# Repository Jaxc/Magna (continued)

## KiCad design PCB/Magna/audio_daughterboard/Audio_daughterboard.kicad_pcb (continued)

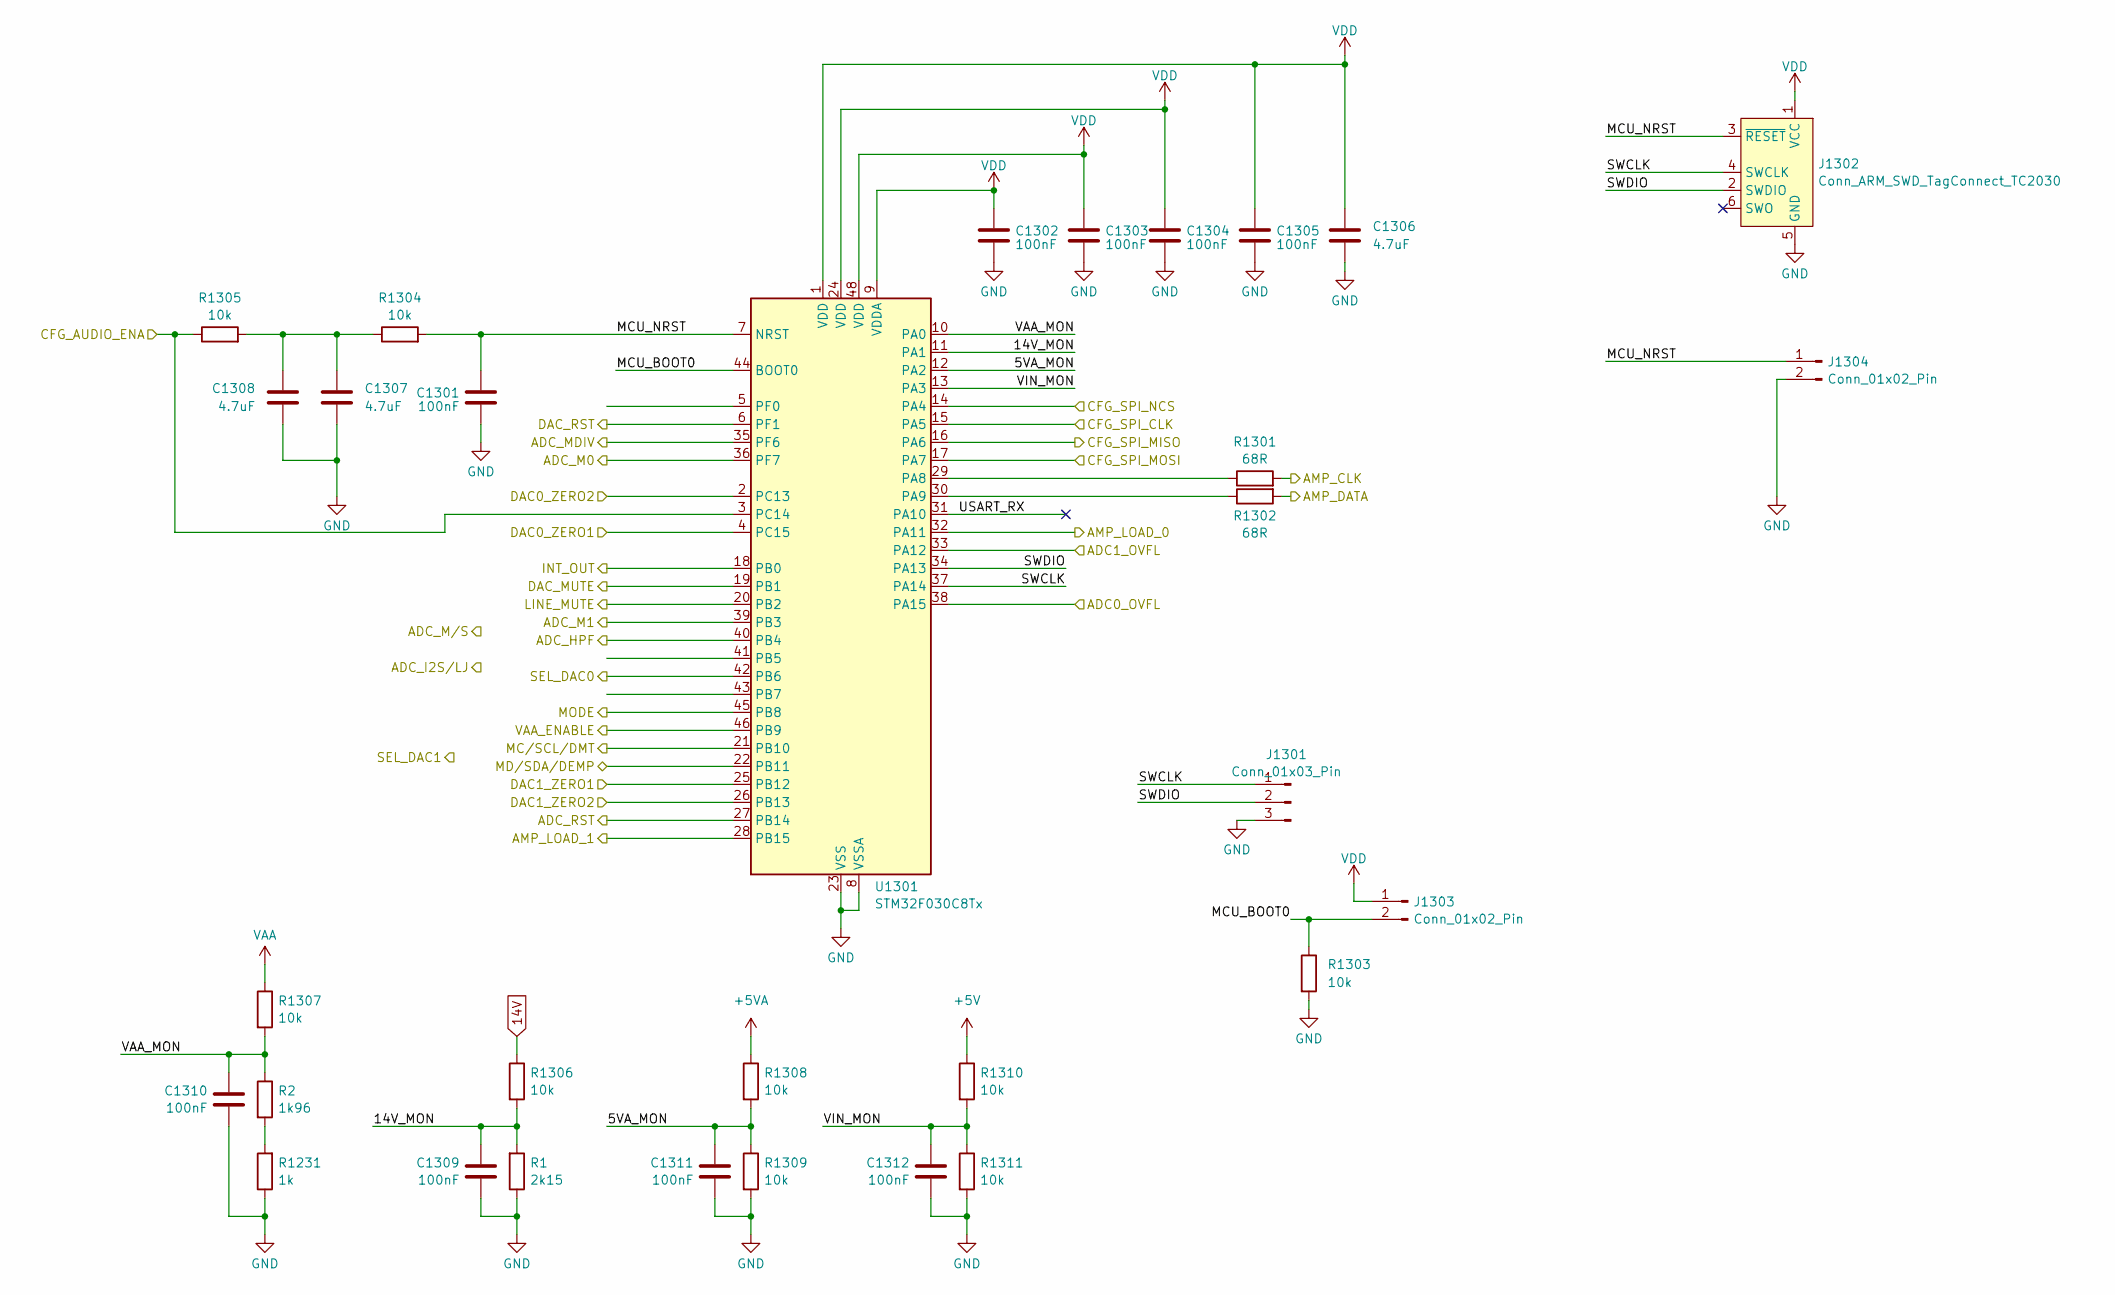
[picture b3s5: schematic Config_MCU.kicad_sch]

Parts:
C1301, C1302, C1303, C1304, C1305, C1309, C1310, C1311, C1312: 100nF; C_0603_1608Metric; LCSC C14663
C1306, C1307, C1308: 4.7uF; C_1206_3216Metric; LCSC C29823
J1301: Conn_01x03_Pin; PinHeader_1x03_P2.54mm_Vertical
J1302: Conn_ARM_SWD_TagConnect_TC2030; Tag-Connect_TC2030-IDC-FP_2x03_P1.27mm_Vertical
J1303, J1304: Conn_01x02_Pin; PinHeader_1x02_P2.54mm_Vertical
R1: 2k15; R_0603_1608Metric; LCSC C667562
R2: 1k96; R_0603_1608Metric; LCSC C160602
R1231: 1k; R_0603_1608Metric; LCSC C110776
R1301, R1302: 68R; R_0603_1608Metric; LCSC C351632
R1303, R1304, R1305, R1306, R1307, R1308, R1309, R1310, R1311: 10k; R_0603_1608Metric; LCSC C95204
U1301: STM32F030C8Tx; LQFP-48_7x7mm_P0.5mm; LCSC C23922

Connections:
14V: R1306.1; also elsewhere on the board
+5V: R1310.1; also elsewhere on the board
+5VA: R1308.1; also elsewhere on the board
/AUDIO_CFG_INT: U1301.18 (PB0); also elsewhere on the board
/AudioAdc0/ADC_HPF: U1301.40 (PB4); also elsewhere on the board
/AudioAdc0/ADC_M0: U1301.36 (PF7); also elsewhere on the board
/AudioAdc0/ADC_M1: U1301.39 (PB3); also elsewhere on the board
/AudioAdc0/ADC_MDIV: U1301.35 (PF6); also elsewhere on the board
/AudioAdc0/ADC_OVFL: U1301.38 (PA15); also elsewhere on the board
/AudioAdc0/ADC_RST: U1301.27 (PB14); also elsewhere on the board
/AudioAdc0/AMP_CLK: R1301.2; also elsewhere on the board
/AudioAdc0/AMP_DATA: R1302.2; also elsewhere on the board
/AudioAdc0/AMP_LOAD: U1301.32 (PA11); also elsewhere on the board
/AudioAdc1/ADC_OVFL: U1301.33 (PA12); also elsewhere on the board
/AudioAdc1/AMP_LOAD: U1301.28 (PB15); also elsewhere on the board
/AudioDac0/MC/SCL/DMT: U1301.21 (PB10); also elsewhere on the board
/AudioDac0/MD/SDA/DEMP: U1301.22 (PB11); also elsewhere on the board
/AudioDac0/MUTE: U1301.19 (PB1); also elsewhere on the board
/AudioDac0/ZERO1: U1301.25 (PB12); also elsewhere on the board
/AudioDac0/ZERO2: U1301.26 (PB13); also elsewhere on the board
/AudioDac0/~RST: U1301.6 (PF1); also elsewhere on the board
/AudioDac1/ZERO1: U1301.4 (PC15); also elsewhere on the board
/AudioDac1/ZERO2: U1301.2 (PC13); also elsewhere on the board
/CFG_AUDIO_ENA: R1305.1, U1301.3 (PC14); also elsewhere on the board
/CFG_SPI_CLK: U1301.15 (PA5); also elsewhere on the board
/CFG_SPI_MISO: U1301.16 (PA6); also elsewhere on the board
/CFG_SPI_MOSI: U1301.17 (PA7); also elsewhere on the board
/CFG_SPI_NCS: U1301.14 (PA4); also elsewhere on the board
/Config MCU/5VA_MON: C1311.1, R1308.2, R1309.1, U1301.12 (PA2)
/Config MCU/14V_MON: C1309.1, R1.2, R1306.2, U1301.11 (PA1)
/Config MCU/LINE_MUTE: U1301.20 (PB2); also elsewhere on the board
/Config MCU/MCU_BOOT0: J1303.2, R1303.1, U1301.44 (BOOT0)
/Config MCU/MCU_NRST: C1301.1, J1302.3 (~RESET), J1304.1, R1304.2, U1301.7 (NRST)
/Config MCU/MODE: U1301.45 (PB8)
/Config MCU/SEL_DAC0: U1301.42 (PB6)
/Config MCU/SWCLK: J1301.1, J1302.4 (SWCLK), U1301.37 (PA14)
/Config MCU/SWDIO: J1301.2, J1302.2 (SWDIO), U1301.34 (PA13)
/Config MCU/USART_RX: U1301.31 (PA10)
/Config MCU/VAA_MON: C1310.1, R2.1, R1307.2, U1301.10 (PA0)
/Config MCU/VIN_MON: C1312.1, R1310.2, R1311.1, U1301.13 (PA3)
/VAA_EN: U1301.46 (PB9); also elsewhere on the board
GND: C1301.2, C1302.2, C1303.2, C1304.2, C1305.2, C1306.2, C1307.2, C1308.2, C1309.2, C1310.2, C1311.2, C1312.2, J1301.3, J1302.5 (GND), J1304.2, R1.1, R1231.1, R1303.2, R1309.2, R1311.2, U1301.8 (VSSA), U1301.23 (VSS), U1301.47 (VSS); also elsewhere on the board
unnamed: C1307.1, C1308.1, R1304.1, R1305.2
unnamed: R2.2, R1231.2
unnamed: R1301.1, U1301.29 (PA8)
unnamed: R1302.1, U1301.30 (PA9)
VAA: R1307.1; also elsewhere on the board
VDD: C1302.1, C1303.1, C1304.1, C1305.1, C1306.1, J1302.1 (VCC), J1303.1, U1301.1 (VDD), U1301.9 (VDDA), U1301.24 (VDD), U1301.48 (VDD); also elsewhere on the board

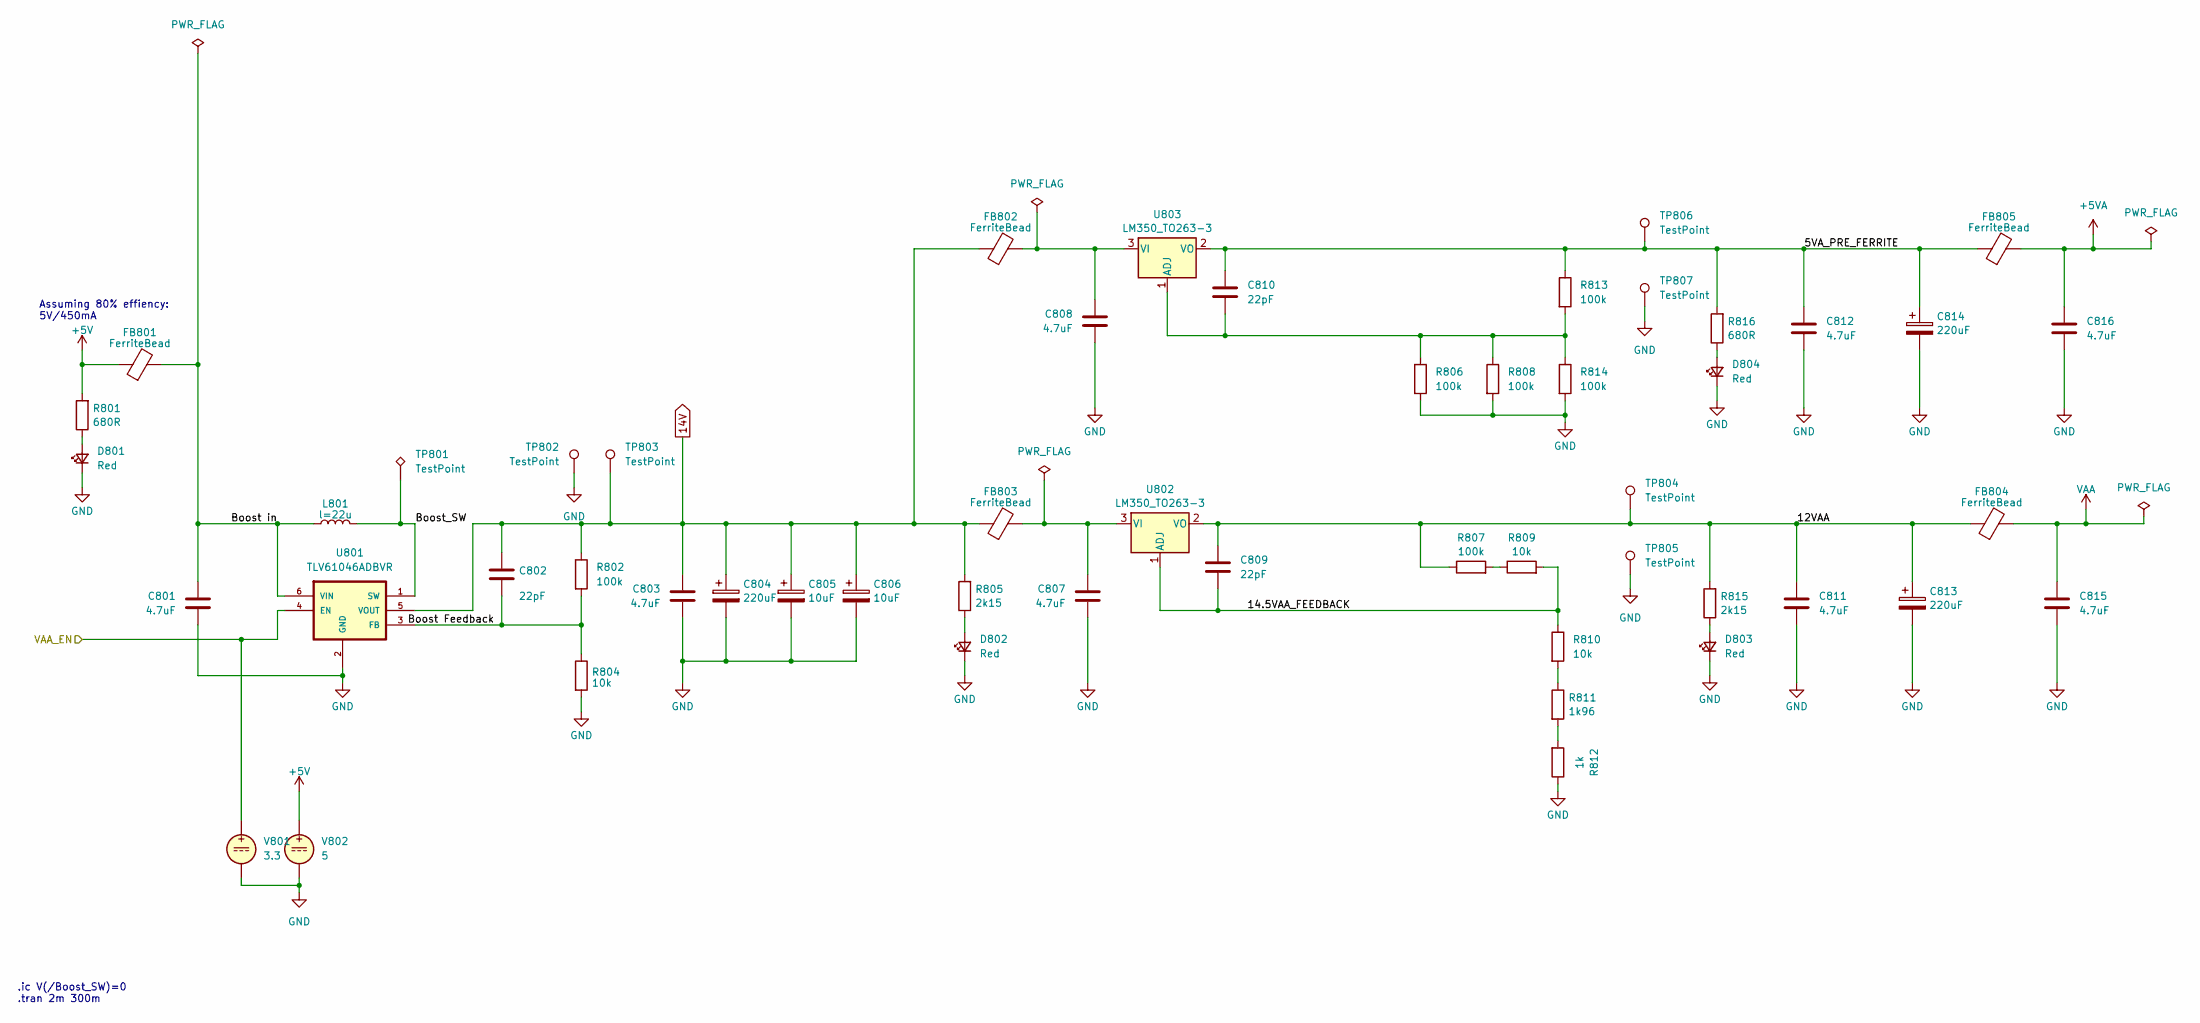
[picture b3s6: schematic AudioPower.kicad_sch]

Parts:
C801, C803, C807, C808, C811, C812, C815, C816: 4.7uF; C_1206_3216Metric; LCSC C29823
C802: 22pF; C_0603_1608Metric; Voltage 50V; LCSC C1653
C804, C813, C814: 220uF; CP_Elec_4x5.8; LCSC C729680
C805, C806: 10uF; CP_Elec_4x5.8; LCSC C2163094
C809, C810: 22pF; C_0603_1608Metric; LCSC C1653
D801, D802, D803, D804: Red; LED_0805_2012Metric; LCSC C84256
FB801, FB802, FB803, FB804, FB805: FerriteBead; L_0805_2012Metric; LCSC C1015
L801: l=22u; MSCD43; LCSC C915172
R801, R816: 680R; R_0603_1608Metric; LCSC C2989042
R802, R806, R807, R808, R813, R814: 100k; R_0603_1608Metric; LCSC C25803
R804, R809, R810: 10k; R_0603_1608Metric; LCSC C95204
R805, R815: 2k15; R_0603_1608Metric; LCSC C667562
R811: 1k96; R_0603_1608Metric; LCSC C160602
R812: 1k; R_0603_1608Metric; LCSC C110776
TP801: TestPoint; TestPoint_Pad_1.0x1.0mm
TP802, TP803, TP804, TP805, TP806, TP807: TestPoint; TestPoint_Keystone_5005-5009_Compact
U801: TLV61046ADBVR; TSOT-23-6_HandSoldering; LCSC C464815
U802, U803: LM350_TO263-3; TO-263-3_TabPin2; LCSC C512786
V801: 3.3
V802: 5

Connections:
14V: C802.1, C803.1, C804.1, C805.1, C806.1, FB802.1, FB803.1, R802.1, R805.2, TP803.1, U801.5 (VOUT); also elsewhere on the board
+5V: FB801.1, R801.2, V802.1; also elsewhere on the board
+5VA: C816.1, FB805.2; also elsewhere on the board
/AudioPower/5VA_PRE_FERRITE: C810.1, C812.1, C814.1, FB805.1, R813.1, R816.2, TP806.1, U803.2 (VO)
/AudioPower/12VAA: C809.1, C811.1, C813.1, FB804.1, R807.1, R815.2, TP804.1, U802.2 (VO)
/AudioPower/14.5VAA_FEEDBACK: C809.2, R809.2, R810.1, U802.1 (ADJ)
/AudioPower/Boost Feedback: C802.2, R802.2, R804.1, U801.3 (FB)
/AudioPower/Boost in: C801.1, FB801.2, L801.1, U801.6 (VIN)
/AudioPower/Boost_SW: L801.2, TP801.1, U801.1 (SW)
/VAA_EN: U801.4 (EN), V801.1; also elsewhere on the board
GND: C801.2, C803.2, C804.2, C805.2, C806.2, C807.2, C808.2, C811.2, C812.2, C813.2, C814.2, C815.2, C816.2, D801.1 (K), D802.1 (K), D803.1 (K), D804.1 (K), R804.2, R806.2, R808.2, R812.1, R814.2, TP802.1, TP805.1, TP807.1, U801.2 (GND), V801.2, V802.2; also elsewhere on the board
unnamed: D801.2 (A), R801.1
unnamed: D802.2 (A), R805.1
unnamed: D803.2 (A), R815.1
unnamed: D804.2 (A), R816.1
unnamed: R807.2, R809.1
unnamed: R810.2, R811.1
unnamed: R811.2, R812.2
unnamed: C807.1, FB803.2, U802.3 (VI)
unnamed: C810.2, R806.1, R808.1, R813.2, R814.1, U803.1 (ADJ)
unnamed: C808.1, FB802.2, U803.3 (VI)
VAA: C815.1, FB804.2; also elsewhere on the board

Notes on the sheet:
Assuming 80% effiency: 5V/450mA
.ic V(/Boost_SW)=0 .tran 2m 300m

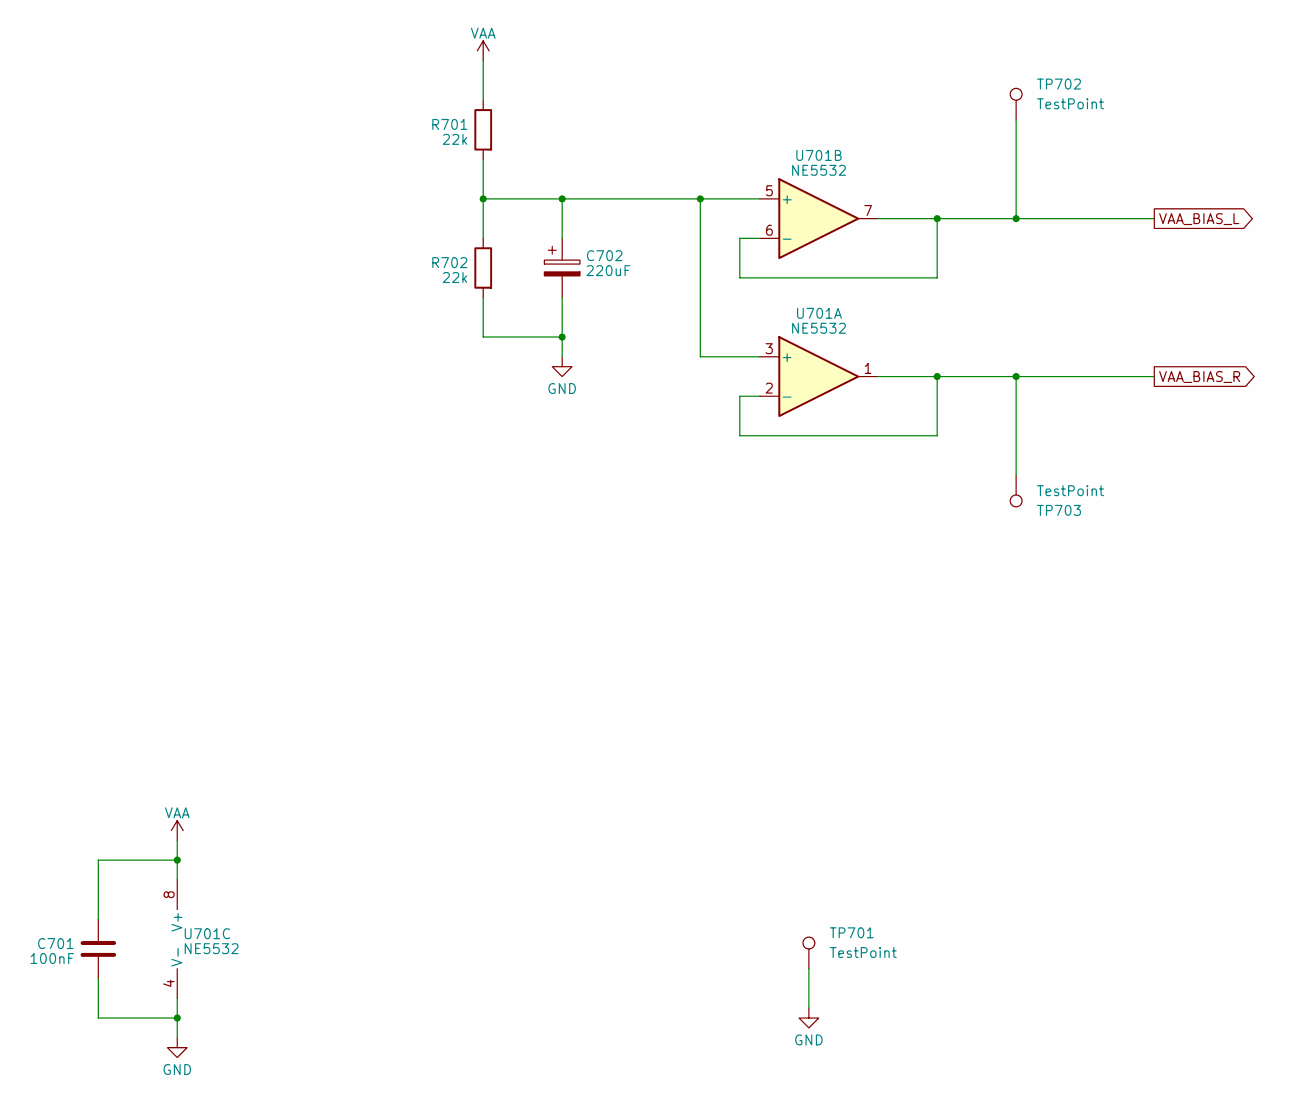
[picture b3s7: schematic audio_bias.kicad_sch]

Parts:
C701: 100nF; C_0603_1608Metric; LCSC C14663
C702: 220uF; CP_Elec_4x5.8; LCSC C729680
R701, R702: 22k; R_0603_1608Metric; LCSC C335085
TP701, TP702, TP703: TestPoint; TestPoint_Keystone_5005-5009_Compact
U701: NE5532; SOIC-8_3.9x4.9mm_P1.27mm; LCSC C7426

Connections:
GND: C701.2, C702.2, R702.2, TP701.1, U701.4 (V-); also elsewhere on the board
unnamed: C702.1, R701.2, R702.1, U701.3 (+), U701.5 (+)
VAA: C701.1, R701.1, U701.8 (V+); also elsewhere on the board
VAA_BIAS_L: TP702.1, U701.6 (-), U701.7; also elsewhere on the board
VAA_BIAS_R: TP703.1, U701.1, U701.2 (-); also elsewhere on the board

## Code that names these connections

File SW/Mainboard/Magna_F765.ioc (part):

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Mcu.Name=STM32F765V(G-I)Tx
Mcu.Package=LQFP100
Mcu.UserName=STM32F765VGTx
PA0/WKUP.Signal=ADCx_IN0
PA1.Signal=ADCx_IN1
PA10.GPIOParameters=GPIO_Label
PA10.GPIO_Label=HSW_EN
PA10.Signal=GPIO_Output
PA11.Mode=Host_Only
PA11.Signal=USB_OTG_FS_DM
PA12.Mode=Host_Only
PA12.Signal=USB_OTG_FS_DP
PA13.Mode=Trace_Asynchronous_SW
PA13.Signal=SYS_JTMS-SWDIO
PA14.Mode=Trace_Asynchronous_SW
PA14.Signal=SYS_JTCK-SWCLK
PA15.Mode=Half_Duplex_Slave
PA15.Signal=I2S3_WS
PA2.Signal=ADCx_IN2
PA3.Mode=OTG/Dual-Role-Device-HS
PA3.Signal=USB_OTG_HS_ULPI_D0
PA4.Signal=ADCx_IN4
PA5.Mode=OTG/Dual-Role-Device-HS
PA5.Signal=USB_OTG_HS_ULPI_CK
PA6.Signal=ADCx_IN6
PA7.GPIOParameters=GPIO_Speed,PinState,GPIO_Label
PA7.GPIO_Label=OE_output_ena
PA7.GPIO_Speed=GPIO_SPEED_FREQ_MEDIUM
PA7.PinState=GPIO_PIN_RESET
PA7.Signal=GPIO_Output
PA8.Mode=Clock-out-1
PA8.Signal=RCC_MCO_1
PB0.Mode=OTG/Dual-Role-Device-HS
PB0.Signal=USB_OTG_HS_ULPI_D1
PB1.Mode=OTG/Dual-Role-Device-HS
PB1.Signal=USB_OTG_HS_ULPI_D2
PB10.Mode=OTG/Dual-Role-Device-HS
PB10.Signal=USB_OTG_HS_ULPI_D3
PB11.Mode=OTG/Dual-Role-Device-HS
PB11.Signal=USB_OTG_HS_ULPI_D4
PB12.Mode=OTG/Dual-Role-Device-HS
PB12.Signal=USB_OTG_HS_ULPI_D5
PB13.Mode=OTG/Dual-Role-Device-HS
PB13.Signal=USB_OTG_HS_ULPI_D6
PB14.Signal=USB_OTG_HS_DM
PB15.Signal=USB_OTG_HS_DP
PB2.Mode=Single Bank 2
PB2.Signal=QUADSPI_CLK
PB3.Mode=Trace_Asynchronous_SW
PB3.Signal=SYS_JTDO-SWO
PB4.GPIOParameters=GPIO_Speed
PB4.GPIO_Speed=GPIO_SPEED_FREQ_VERY_HIGH
PB4.Mode=Half_Duplex_Slave
PB4.Signal=I2S2_WS
PB5.Mode=OTG/Dual-Role-Device-HS
PB5.Signal=USB_OTG_HS_ULPI_D7
PB6.GPIOParameters=GPIO_Label
PB6.GPIO_Label=SCL/ADC_IWL
PB6.Mode=I2C
PB6.Signal=I2C4_SCL
PB7.GPIOParameters=GPIO_Label
PB7.GPIO_Label=SDA/ADC_FSAMPEN
PB7.Mode=I2C
PB7.Signal=I2C4_SDA
PB8.Mode=I2C
PB8.Signal=I2C1_SCL
PB9.Mode=I2C
PB9.Signal=I2C1_SDA
PC0.Mode=OTG/Dual-Role-Device-HS
PC0.Signal=USB_OTG_HS_ULPI_STP
PC1.GPIOParameters=GPIO_Speed
PC1.GPIO_Speed=GPIO_SPEED_FREQ_VERY_HIGH
PC1.Mode=Half_Duplex_Slave
PC1.Signal=I2S2_SD
PC10.Mode=Half_Duplex_Slave
PC10.Signal=I2S3_CK
PC11.Mode=Single Bank 2
PC11.Signal=QUADSPI_BK2_NCS
PC12.GPIOParameters=GPIO_Speed
PC12.GPIO_Speed=GPIO_SPEED_FREQ_VERY_HIGH
PC12.Mode=Half_Duplex_Slave
PC12.Signal=I2S3_SD
PC14/OSC32_IN.GPIOParameters=GPIO_Label
PC14/OSC32_IN.GPIO_Label=USB_PHY_RESET
PC14/OSC32_IN.Signal=GPIO_Output
PC15/OSC32_OUT.GPIOParameters=GPIO_Label
PC15/OSC32_OUT.GPIO_Label=ADC_FORMAT
PC15/OSC32_OUT.Signal=GPIO_Output
PC2.Mode=OTG/Dual-Role-Device-HS
PC2.Signal=USB_OTG_HS_ULPI_DIR
PC3.Mode=OTG/Dual-Role-Device-HS
PC3.Signal=USB_OTG_HS_ULPI_NXT
PC4.Signal=ADCx_IN14
PC5.GPIOParameters=GPIO_Label
PC5.GPIO_Label=VBUS_ADC
PC5.Signal=ADCx_IN15
PC7.Signal=S_TIM3_CH2
PC9.Mode=Audio_ClockIn
PC9.Signal=I2S_CKIN
PD1.GPIOParameters=GPIO_Label
PD1.GPIO_Label=VBUS_OUT_FLG
PD1.Signal=GPXTI1
PD11.Mode=SAI_A_SyncSlave
PD11.Signal=SAI2_SD_A
PD12.GPIOParameters=GPIO_Label
PD12.GPIO_Label=Pot_sel_0
PD12.Signal=S_TIM4_CH1
PD13.GPIOParameters=GPIO_Label
PD13.GPIO_Label=Pot_sel_1
PD13.Signal=S_TIM4_CH2
PD15.GPIOParameters=GPIO_Label
PD15.GPIO_Label=ADC_M_S
PD15.Signal=GPIO_Output
PD3.GPIOParameters=GPIO_Speed
PD3.GPIO_Speed=GPIO_SPEED_FREQ_VERY_HIGH
PD3.Mode=Half_Duplex_Slave
PD3.Signal=I2S2_CK
PD6.GPIOParameters=GPIO_Label
PD6.GPIO_Label=Button_interrupt
PD6.Signal=GPXTI6
PD8.GPIOParameters=GPIO_Label
PD8.GPIO_Label=MIDI_TX
PD8.Mode=Asynchronous
PD8.Signal=USART3_TX
PD9.GPIOParameters=GPIO_Label
PD9.GPIO_Label=MIDI_RX
PD9.Mode=Asynchronous
PD9.Signal=USART3_RX
PE0.GPIOParameters=GPIO_Label
PE0.GPIO_Label=USB_A_PWR_EN
PE0.Signal=GPIO_Output
PE1.GPIOParameters=GPIO_Label
PE1.GPIO_Label=VA_en
PE1.Signal=GPIO_Output
PE10.Mode=Single Bank 2
PE10.Signal=QUADSPI_BK2_IO3
PE11.Mode=SAI_B_SyncSlave
PE11.Signal=SAI2_SD_B
PE12.GPIOParameters=GPIO_Label
PE12.GPIO_Label=serial_CLK
PE12.Mode=TX_Only_Simplex_Unidirect_Master
PE12.Signal=SPI4_SCK
PE13.GPIOParameters=GPIO_Label
PE13.GPIO_Label=serial_CLR
PE13.Signal=GPIO_Output
PE14.GPIOParameters=GPIO_Label
PE14.GPIO_Label=serial_data
PE14.Mode=TX_Only_Simplex_Unidirect_Master
PE14.Signal=SPI4_MOSI
PE2.Mode=SAI_A_MasterWithClock
PE2.Signal=SAI1_MCLK_A
PE3.GPIOParameters=GPIO_Speed
PE3.GPIO_Speed=GPIO_SPEED_FREQ_VERY_HIGH
PE3.Mode=SAI_B_SyncSlave
PE3.Signal=SAI1_SD_B
PE4.GPIOParameters=GPIO_Speed
PE4.GPIO_Speed=GPIO_SPEED_FREQ_VERY_HIGH
PE4.Mode=SAI_A_MasterWithClock
PE4.Signal=SAI1_FS_A
PE5.GPIOParameters=GPIO_Speed
PE5.GPIO_Speed=GPIO_SPEED_FREQ_VERY_HIGH
PE5.Mode=SAI_A_MasterWithClock
PE5.Signal=SAI1_SCK_A
PE6.GPIOParameters=GPIO_Speed
PE6.GPIO_Speed=GPIO_SPEED_FREQ_VERY_HIGH
PE6.Mode=SAI_A_MasterWithClock
PE6.Signal=SAI1_SD_A
PE7.Mode=Single Bank 2
PE7.Signal=QUADSPI_BK2_IO0
PE8.Mode=Single Bank 2
PE8.Signal=QUADSPI_BK2_IO1
PE9.Mode=Single Bank 2
PE9.Signal=QUADSPI_BK2_IO2
PH0/OSC_IN.Mode=HSE-External-Oscillator
PH0/OSC_IN.Signal=RCC_OSC_IN
PH1/OSC_OUT.Mode=HSE-External-Oscillator
PH1/OSC_OUT.Signal=RCC_OSC_OUT
RCC.HSE_VALUE=25000000
RCC.SYSCLKFreq_VALUE=216000000
RCC.SYSCLKSource=RCC_SYSCLKSOURCE_PLLCLK
board=custom

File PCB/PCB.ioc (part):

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Mcu.Name=STM32F765V(G-I)Tx
Mcu.Package=LQFP100
Mcu.UserName=STM32F765VGTx
PA0/WKUP.Signal=ADCx_IN0
PA1.Signal=ADCx_IN1
PA11.Mode=Host_Only
PA11.Signal=USB_OTG_FS_DM
PA12.Mode=Host_Only
PA12.Signal=USB_OTG_FS_DP
PA13.Mode=JTAG_4_pins
PA13.Signal=SYS_JTMS-SWDIO
PA14.Mode=JTAG_4_pins
PA14.Signal=SYS_JTCK-SWCLK
PA15.Mode=JTAG_4_pins
PA15.Signal=SYS_JTDI
PA2.Signal=ADCx_IN2
PA3.Mode=Device_HS
PA3.Signal=USB_OTG_HS_ULPI_D0
PA4.Mode=Half_Duplex_Slave
PA4.Signal=I2S3_WS
PA5.Mode=Device_HS
PA5.Signal=USB_OTG_HS_ULPI_CK
PA6.Signal=ADCx_IN6
PA8.Mode=Clock-out-1
PA8.Signal=RCC_MCO_1
PA9.Mode=Half_Duplex_Slave
PA9.Signal=I2S2_CK
PB0.Mode=Device_HS
PB0.Signal=USB_OTG_HS_ULPI_D1
PB1.Mode=Device_HS
PB1.Signal=USB_OTG_HS_ULPI_D2
PB10.Mode=Device_HS
PB10.Signal=USB_OTG_HS_ULPI_D3
PB11.Mode=Device_HS
PB11.Signal=USB_OTG_HS_ULPI_D4
PB12.Mode=Device_HS
PB12.Signal=USB_OTG_HS_ULPI_D5
PB13.Mode=Device_HS
PB13.Signal=USB_OTG_HS_ULPI_D6
PB14.GPIOParameters=GPIO_Label
PB14.GPIO_Label=OE_output_ena
PB14.Signal=GPIO_Output
PB15.Mode=Half_Duplex_Slave
PB15.Signal=I2S2_SD
PB2.Mode=Single Bank 2
PB2.Signal=QUADSPI_CLK
PB3.Mode=JTAG_4_pins
PB3.Signal=SYS_JTDO-SWO
PB5.Mode=Device_HS
PB5.Signal=USB_OTG_HS_ULPI_D7
PB6.Mode=I2C
PB6.Signal=I2C1_SCL
PB7.Mode=I2C
PB7.Signal=I2C1_SDA
PB9.Mode=Half_Duplex_Slave
PB9.Signal=I2S2_WS
PC0.Mode=Device_HS
PC0.Signal=USB_OTG_HS_ULPI_STP
PC1.Signal=ADCx_IN11
PC10.Mode=Half_Duplex_Slave
PC10.Signal=I2S3_CK
PC11.Mode=Single Bank 2
PC11.Signal=QUADSPI_BK2_NCS
PC12.Mode=Asynchronous
PC12.Signal=UART5_TX
PC13.GPIOParameters=GPIO_Label
PC13.GPIO_Label=HSW_EN
PC13.Signal=GPIO_Output
PC14/OSC32_IN.GPIOParameters=GPIO_Label
PC14/OSC32_IN.GPIO_Label=USB_PHY_RESET
PC14/OSC32_IN.Signal=GPIO_Output
PC15/OSC32_OUT.GPIOParameters=GPIO_Label
PC15/OSC32_OUT.GPIO_Label=ADC_FORMAT
PC15/OSC32_OUT.Signal=GPIO_Output
PC2.Mode=Device_HS
PC2.Signal=USB_OTG_HS_ULPI_DIR
PC3.Mode=Device_HS
PC3.Signal=USB_OTG_HS_ULPI_NXT
PC4.Signal=ADCx_IN14
PC5.GPIOParameters=GPIO_Label
PC5.GPIO_Label=VBUS_ADC
PC5.Signal=ADCx_IN15
PC9.Mode=Audio_ClockIn
PC9.Signal=I2S_CKIN
PD1.GPIOParameters=GPIO_Label
PD1.GPIO_Label=VBUS_OUT_FLG
PD1.Signal=GPXTI1
PD11.Mode=SAI_A_SyncSlave
PD11.Signal=SAI2_SD_A
PD12.GPIOParameters=GPIO_Label
PD12.GPIO_Label=Pot_sel_0
PD12.Signal=S_TIM4_CH1
PD13.GPIOParameters=GPIO_Label
PD13.GPIO_Label=Pot_sel_1
PD13.Signal=S_TIM4_CH2
PD2.Mode=Asynchronous
PD2.Signal=UART5_RX
PD5.GPIOParameters=GPIO_Label
PD5.GPIO_Label=ADC_IWL
PD5.Signal=GPIO_Output
PD6.Mode=Half_Duplex_Slave
PD6.Signal=I2S3_SD
PD7.GPIOParameters=GPIO_Label
PD7.GPIO_Label=ADC_FSAMPEN
PD7.Signal=GPIO_Output
PD8.GPIOParameters=GPIO_Label
PD8.GPIO_Label=button_interrupt
PD8.Signal=GPXTI8
PD9.GPIOParameters=GPIO_Label
PD9.GPIO_Label=ADC_M_S
PD9.Signal=GPIO_Output
PE0.GPIOParameters=GPIO_Label
PE0.GPIO_Label=USB_A_PWR_EN
PE0.Signal=GPIO_Output
PE1.GPIOParameters=GPIO_Label
PE1.GPIO_Label=VA_en
PE1.Signal=GPIO_Output
PE10.Mode=Single Bank 2
PE10.Signal=QUADSPI_BK2_IO3
PE11.Mode=SAI_B_SyncSlave
PE11.Signal=SAI2_SD_B
PE12.GPIOParameters=GPIO_Label
PE12.GPIO_Label=serial_CLK
PE12.Mode=TX_Only_Simplex_Unidirect_Master
PE12.Signal=SPI4_SCK
PE13.GPIOParameters=GPIO_Label
PE13.GPIO_Label=serial_CLR
PE13.Signal=GPIO_Output
PE14.GPIOParameters=GPIO_Label
PE14.GPIO_Label=serial_data
PE14.Mode=TX_Only_Simplex_Unidirect_Master
PE14.Signal=SPI4_MOSI
PE15.Signal=GPIO_Output
PE2.Mode=SAI_A_MasterWithClock
PE2.Signal=SAI1_MCLK_A
PE3.Mode=SAI_B_SyncSlave
PE3.Signal=SAI1_SD_B
PE4.Mode=SAI_A_MasterWithClock
PE4.Signal=SAI1_FS_A
PE5.Mode=SAI_A_MasterWithClock
PE5.Signal=SAI1_SCK_A
PE6.Mode=SAI_A_MasterWithClock
PE6.Signal=SAI1_SD_A
PE7.Mode=Single Bank 2
PE7.Signal=QUADSPI_BK2_IO0
PE8.Mode=Single Bank 2
PE8.Signal=QUADSPI_BK2_IO1
PE9.Mode=Single Bank 2
PE9.Signal=QUADSPI_BK2_IO2
PH0/OSC_IN.Mode=HSE-External-Oscillator
PH0/OSC_IN.Signal=RCC_OSC_IN
PH1/OSC_OUT.Mode=HSE-External-Oscillator
PH1/OSC_OUT.Signal=RCC_OSC_OUT
RCC.HSE_VALUE=24000000
RCC.SYSCLKFreq_VALUE=216000000
RCC.SYSCLKSource=RCC_SYSCLKSOURCE_PLLCLK
board=custom

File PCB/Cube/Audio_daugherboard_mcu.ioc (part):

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Mcu.Name=STM32F030C6Tx
Mcu.Package=LQFP48
Mcu.UserName=STM32F030C6Tx
PA0.GPIOParameters=GPIO_Label
PA0.GPIO_Label=MON_VAA
PA0.Mode=IN0
PA0.Signal=ADC_IN0
PA1.GPIOParameters=GPIO_Label
PA1.GPIO_Label=MON_5VA
PA1.Mode=IN1
PA1.Signal=ADC_IN1
PA10.Mode=Synchronous
PA10.Signal=USART1_RX
PA11.GPIOParameters=GPIO_Label
PA11.GPIO_Label=AMP1_LOAD
PA11.Signal=GPIO_Output
PA12.GPIOParameters=GPIO_Label
PA12.GPIO_Label=ADC1_OVERFLOW
PA12.Signal=GPXTI12
PA13.Mode=Serial_Wire
PA13.Signal=SYS_SWDIO
PA14.Mode=Serial_Wire
PA14.Signal=SYS_SWCLK
PA15.GPIOParameters=GPIO_Label
PA15.GPIO_Label=ADC0_OVFL
PA15.Signal=GPXTI15
PA2.GPIOParameters=GPIO_Label
PA2.GPIO_Label=MON_14V
PA2.Mode=IN2
PA2.Signal=ADC_IN2
PA3.GPIOParameters=GPIO_Label
PA3.GPIO_Label=VIN_MON
PA3.Mode=IN3
PA3.Signal=ADC_IN3
PA4.Mode=NSS_Signal_Hard_Input
PA4.Signal=SPI1_NSS
PA5.Mode=Full_Duplex_Slave
PA5.Signal=SPI1_SCK
PA6.Mode=Full_Duplex_Slave
PA6.Signal=SPI1_MISO
PA7.Mode=Full_Duplex_Slave
PA7.Signal=SPI1_MOSI
PA8.Mode=Synchronous
PA8.Signal=USART1_CK
PA9.Mode=Synchronous
PA9.Signal=USART1_TX
PB0.GPIOParameters=GPIO_Label
PB0.GPIO_Label=INT_OUT
PB0.Signal=GPIO_Output
PB1.GPIOParameters=GPIO_Label
PB1.GPIO_Label=LINE_MUTE
PB1.Signal=GPIO_Output
PB10.Mode=I2C
PB10.Signal=I2C1_SCL
PB11.Mode=I2C
PB11.Signal=I2C1_SDA
PB12.GPIOParameters=GPIO_Label
PB12.GPIO_Label=ADC_M_S
PB12.Signal=GPIO_Output
PB13.GPIOParameters=GPIO_Label
PB13.GPIO_Label=ADC_I2S
PB13.Signal=GPIO_Output
PB14.GPIOParameters=GPIO_Label
PB14.GPIO_Label=ADC_RST
PB14.Signal=GPIO_Output
PB15.GPIOParameters=GPIO_Label
PB15.GPIO_Label=AMP0_LOAD
PB15.Signal=GPIO_Output
PB2.GPIOParameters=GPIO_Label
PB2.GPIO_Label=VAA_ENA
PB2.Signal=GPIO_Output
PB3.GPIOParameters=GPIO_Label
PB3.GPIO_Label=DAC_NRST
PB3.Signal=GPIO_Output
PB4.GPIOParameters=GPIO_Label
PB4.GPIO_Label=DAC1_ADDR0
PB4.Signal=GPIO_Output
PB5.GPIOParameters=GPIO_Label
PB5.GPIO_Label=DAC0_ADDR0
PB5.Signal=GPIO_Output
PB6.GPIOParameters=GPIO_Label
PB6.GPIO_Label=ADC_M1
PB6.Signal=GPIO_Output
PB7.GPIOParameters=GPIO_Label
PB7.GPIO_Label=ADC_HPF
PB7.Signal=GPIO_Output
PB8.GPIOParameters=GPIO_Label
PB8.GPIO_Label=DAC_MODE
PB8.Signal=GPIO_Output
PB9.GPIOParameters=GPIO_Label
PB9.GPIO_Label=DAC_MUTE
PB9.Signal=GPIO_Output
PC13.GPIOParameters=GPIO_Label
PC13.GPIO_Label=ADC_MDIV
PC13.Signal=GPIO_Output
PC14-OSC32_IN.GPIOParameters=GPIO_Label
PC14-OSC32_IN.GPIO_Label=CFG_AUDIO_ENA
PC14-OSC32_IN.Signal=GPXTI14
PC15-OSC32_OUT.GPIOParameters=GPIO_Label
PC15-OSC32_OUT.GPIO_Label=ADC_M0
PC15-OSC32_OUT.Signal=GPIO_Output
PF0-OSC_IN.GPIOParameters=GPIO_Label
PF0-OSC_IN.GPIO_Label=DAC1_ZERO2
PF0-OSC_IN.Signal=GPXTI0
PF1-OSC_OUT.GPIOParameters=GPIO_Label
PF1-OSC_OUT.GPIO_Label=DAC1_ZERO1
PF1-OSC_OUT.Signal=GPXTI1
PF6.GPIOParameters=GPIO_Label
PF6.GPIO_Label=DAC0_ZERO2
PF6.Signal=GPIO_Input
PF7.GPIOParameters=GPIO_Label
PF7.GPIO_Label=DAC0_ZERO1
PF7.Signal=GPIO_Input
RCC.SYSCLKFreq_VALUE=48000000
RCC.SYSCLKSource=RCC_SYSCLKSOURCE_PLLCLK
board=custom
